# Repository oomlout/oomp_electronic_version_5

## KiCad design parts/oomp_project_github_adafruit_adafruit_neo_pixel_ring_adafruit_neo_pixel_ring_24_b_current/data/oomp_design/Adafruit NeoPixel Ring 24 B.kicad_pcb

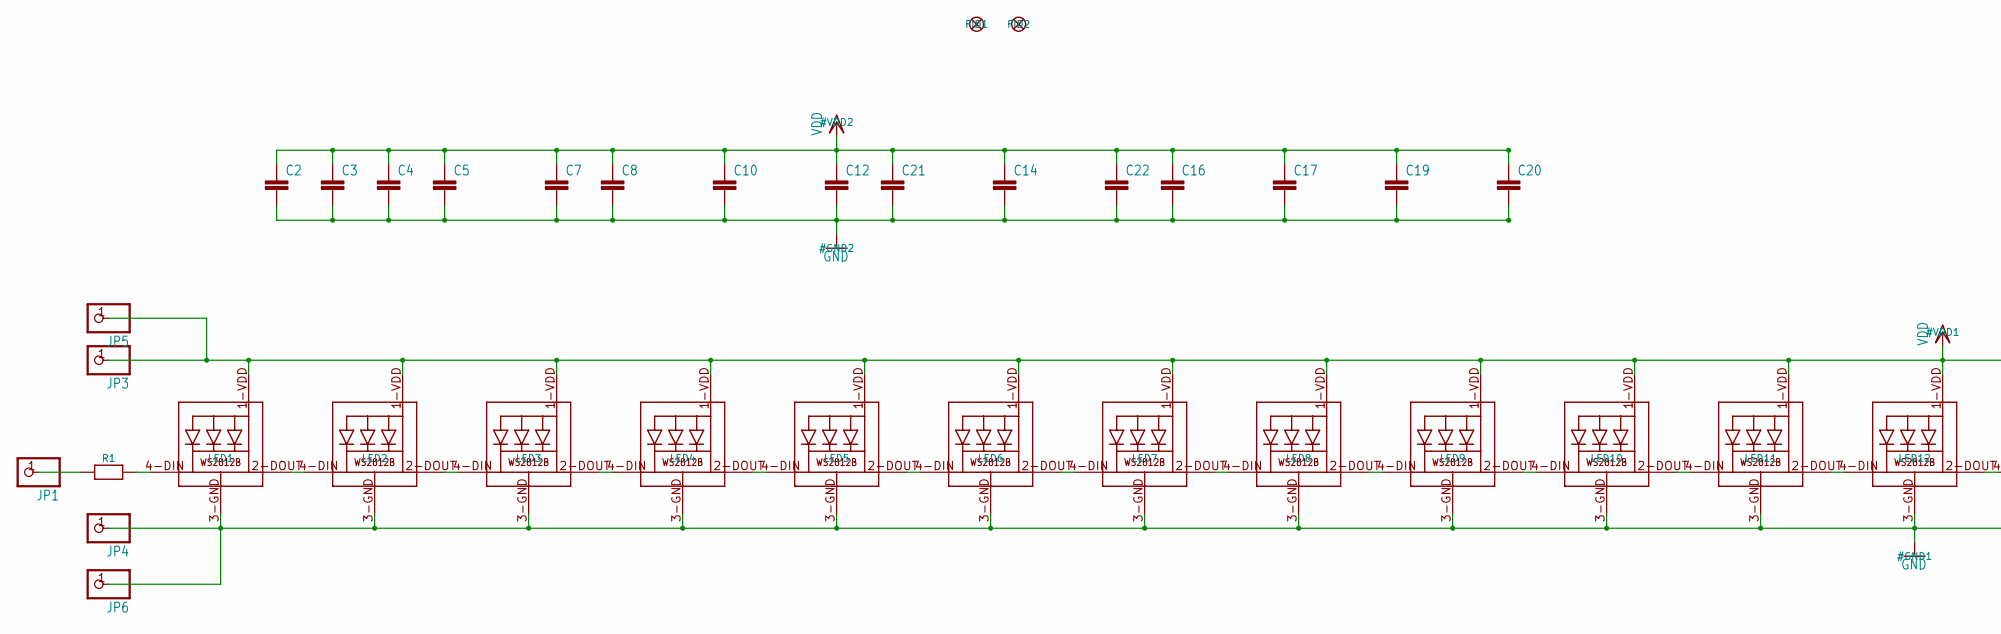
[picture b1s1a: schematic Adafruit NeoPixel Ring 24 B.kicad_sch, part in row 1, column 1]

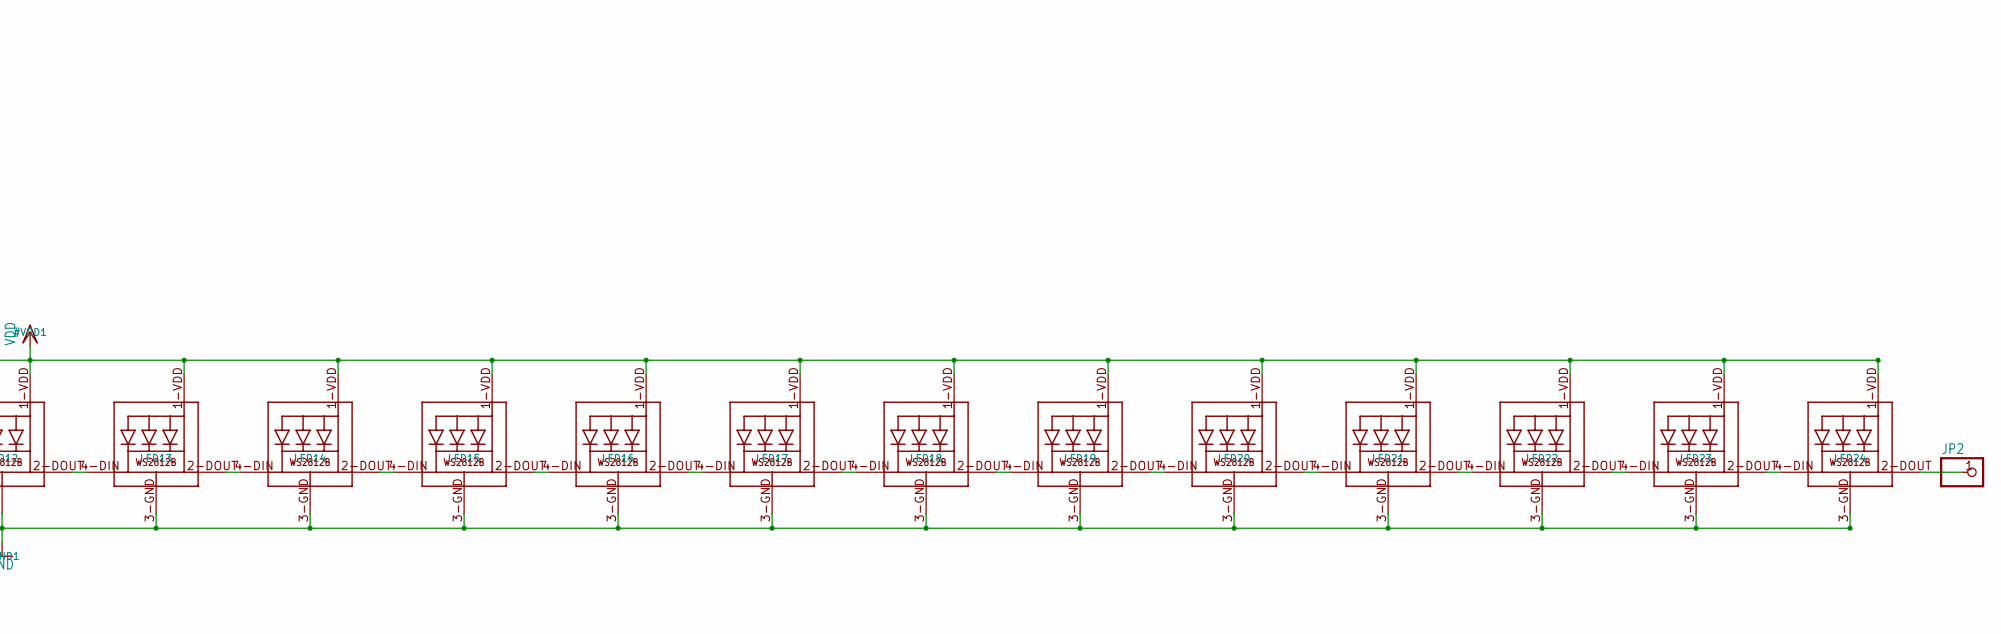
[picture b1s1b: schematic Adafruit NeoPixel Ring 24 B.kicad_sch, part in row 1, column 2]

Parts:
C2, C3, C4, C5, C7, C8, C10, C12, C14, C16, C17, C19, C20, C21, C22: C-EUC0603; C0603
FID1, FID2: FIDUCIAL""; FIDUCIAL_1MM
JP1, JP2, JP3, JP4, JP5, JP6: PINHD-1X1CB; 1X01-CLEANBIG
LED1, LED2, LED3, LED4, LED5, LED6, LED7, LED8, LED9, LED10, LED11, LED12, LED13, LED14, LED15, LED16, LED17, LED18, LED19, LED20, LED21, LED22, LED23, LED24: WS2812B5050; WS2812B
R1: RESISTOR_0603_NOOUT; 0603-NO

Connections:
GND: C2.2, C3.2, C4.2, C5.2, C7.2, C8.2, C10.2, C12.2, C14.2, C16.2, C17.2, C19.2, C20.2, C21.2, C22.2, JP4.1, JP6.1, LED1.3-GND (GND), LED2.3-GND (GND), LED3.3-GND (GND), LED4.3-GND (GND), LED5.3-GND (GND), LED6.3-GND (GND), LED7.3-GND (GND), LED8.3-GND (GND), LED9.3-GND (GND), LED10.3-GND (GND), LED11.3-GND (GND), LED12.3-GND (GND), LED13.3-GND (GND), LED14.3-GND (GND), LED15.3-GND (GND), LED16.3-GND (GND), LED17.3-GND (GND), LED18.3-GND (GND), LED19.3-GND (GND), LED20.3-GND (GND), LED21.3-GND (GND), LED22.3-GND (GND), LED23.3-GND (GND), LED24.3-GND (GND)
unnamed: LED1.2-DOUT (DO), LED2.4-DIN (DI)
unnamed: LED2.2-DOUT (DO), LED3.4-DIN (DI)
unnamed: LED3.2-DOUT (DO), LED4.4-DIN (DI)
unnamed: LED4.2-DOUT (DO), LED5.4-DIN (DI)
unnamed: LED5.2-DOUT (DO), LED6.4-DIN (DI)
unnamed: LED6.2-DOUT (DO), LED7.4-DIN (DI)
unnamed: LED7.2-DOUT (DO), LED8.4-DIN (DI)
unnamed: LED8.2-DOUT (DO), LED9.4-DIN (DI)
unnamed: LED9.2-DOUT (DO), LED10.4-DIN (DI)
unnamed: LED10.2-DOUT (DO), LED11.4-DIN (DI)
unnamed: LED11.2-DOUT (DO), LED12.4-DIN (DI)
unnamed: LED12.2-DOUT (DO), LED13.4-DIN (DI)
unnamed: LED13.2-DOUT (DO), LED14.4-DIN (DI)
unnamed: LED14.2-DOUT (DO), LED15.4-DIN (DI)
unnamed: LED15.2-DOUT (DO), LED16.4-DIN (DI)
unnamed: LED16.2-DOUT (DO), LED17.4-DIN (DI)
unnamed: LED17.2-DOUT (DO), LED18.4-DIN (DI)
unnamed: LED18.2-DOUT (DO), LED19.4-DIN (DI)
unnamed: LED19.2-DOUT (DO), LED20.4-DIN (DI)
unnamed: LED20.2-DOUT (DO), LED21.4-DIN (DI)
unnamed: LED21.2-DOUT (DO), LED22.4-DIN (DI)
unnamed: LED22.2-DOUT (DO), LED23.4-DIN (DI)
unnamed: LED23.2-DOUT (DO), LED24.4-DIN (DI)
unnamed: JP2.1, LED24.2-DOUT (DO)
unnamed: LED1.4-DIN (DI), R1.2
unnamed: JP1.1, R1.1
VDD: C2.1, C3.1, C4.1, C5.1, C7.1, C8.1, C10.1, C12.1, C14.1, C16.1, C17.1, C19.1, C20.1, C21.1, C22.1, JP3.1, JP5.1, LED1.1-VDD (VDD), LED2.1-VDD (VDD), LED3.1-VDD (VDD), LED4.1-VDD (VDD), LED5.1-VDD (VDD), LED6.1-VDD (VDD), LED7.1-VDD (VDD), LED8.1-VDD (VDD), LED9.1-VDD (VDD), LED10.1-VDD (VDD), LED11.1-VDD (VDD), LED12.1-VDD (VDD), LED13.1-VDD (VDD), LED14.1-VDD (VDD), LED15.1-VDD (VDD), LED16.1-VDD (VDD), LED17.1-VDD (VDD), LED18.1-VDD (VDD), LED19.1-VDD (VDD), LED20.1-VDD (VDD), LED21.1-VDD (VDD), LED22.1-VDD (VDD), LED23.1-VDD (VDD), LED24.1-VDD (VDD)

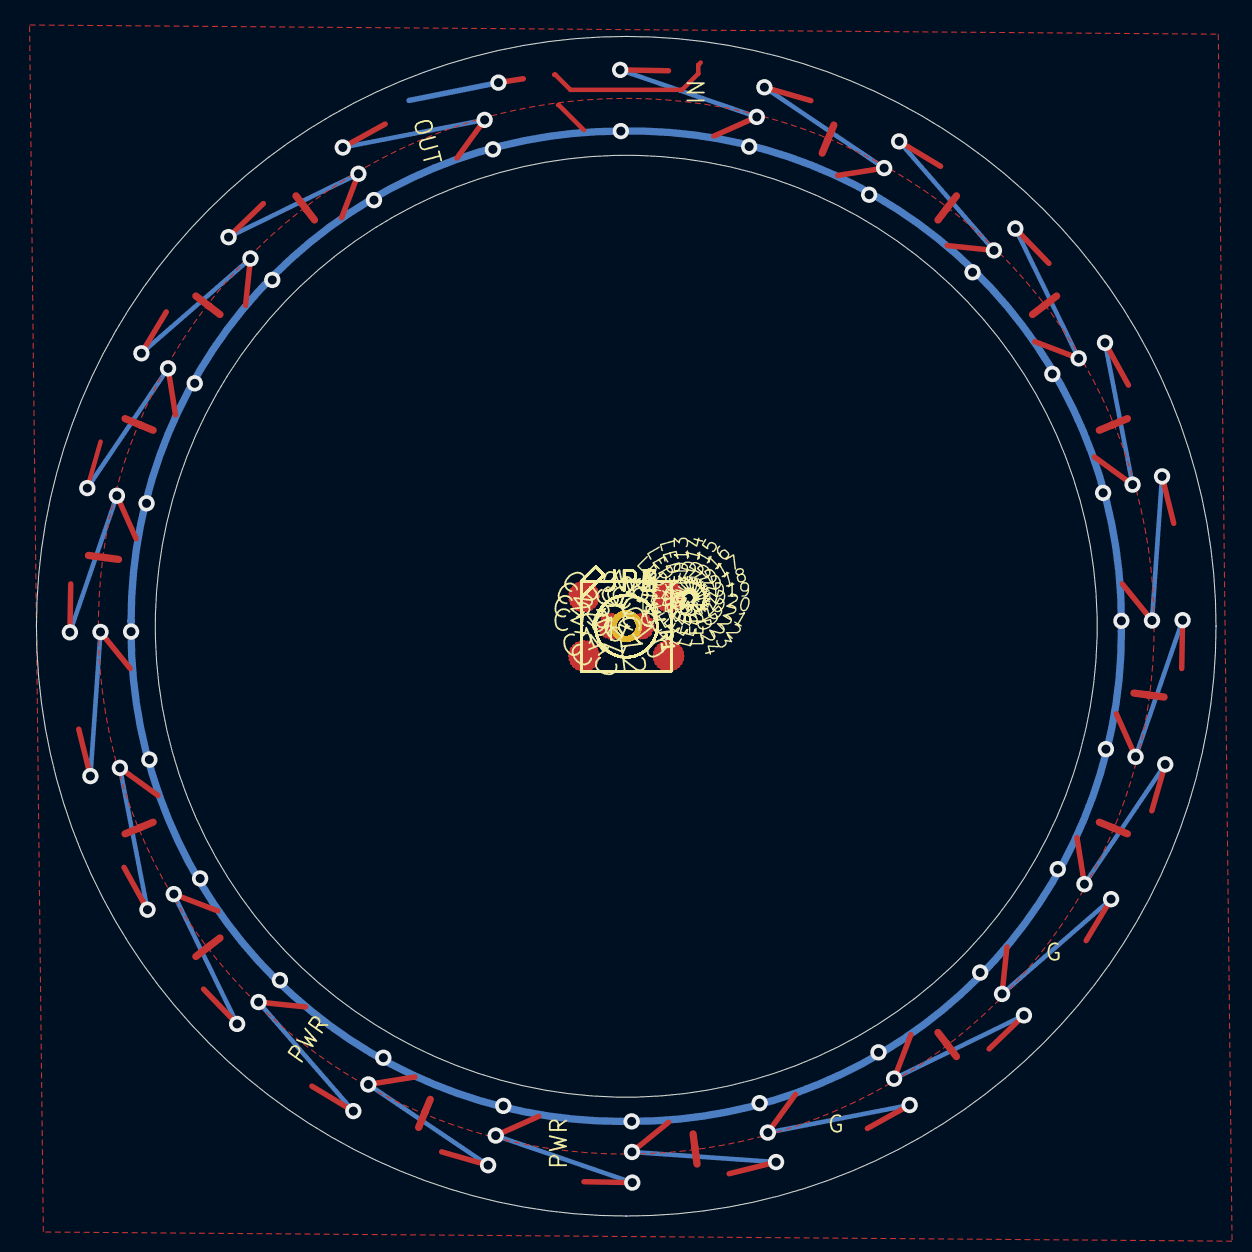
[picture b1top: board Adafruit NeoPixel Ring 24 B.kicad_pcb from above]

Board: 2 copper layers, 65.5 x 65.5 mm, 49 parts (1 on the bottom side), 28 nets.

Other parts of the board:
U$1: ADAFRUIT_5MM

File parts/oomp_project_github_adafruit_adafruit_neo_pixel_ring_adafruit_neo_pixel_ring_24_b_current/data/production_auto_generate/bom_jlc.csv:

Comment,Designator,Footprint,LCSC Part #
,R1,Adafruit NeoPixel Ring 24 B-import-fps:0603-NO,
,"JP1,JP2,JP3,JP4,JP5,JP6",Adafruit NeoPixel Ring 24 B-import-fps:1X01-CLEANBIG,C7501259
,U$1,Adafruit NeoPixel Ring 24 B-import-fps:ADAFRUIT_5MM,
,"C2,C3,C4,C5,C7,C8,C10,C12,C14,C16,C17,C19,C20,C21,C22",Adafruit NeoPixel Ring 24 B-import-fps:C0603,
WS2812B5050,"LED1,LED2,LED3,LED4,LED5,LED6,LED7,LED8,LED9,LED10,LED11,LED12,LED13,LED14,LED15,LED16,LED17,LED18,LED19,LED20,LED21,LED22,LED23,LED24",Adafruit NeoPixel Ring 24 B-import-fps:WS2812B-NARROW,

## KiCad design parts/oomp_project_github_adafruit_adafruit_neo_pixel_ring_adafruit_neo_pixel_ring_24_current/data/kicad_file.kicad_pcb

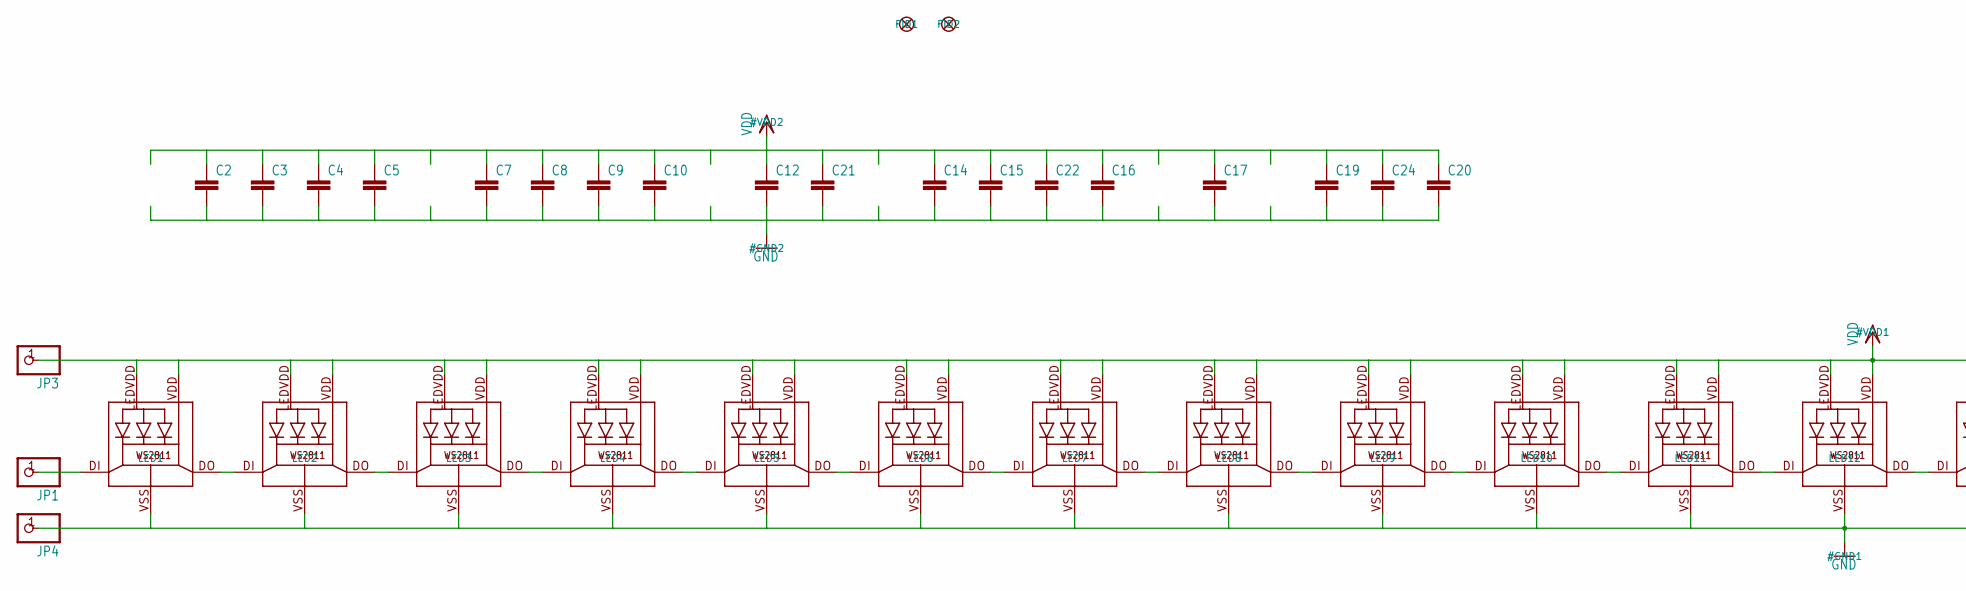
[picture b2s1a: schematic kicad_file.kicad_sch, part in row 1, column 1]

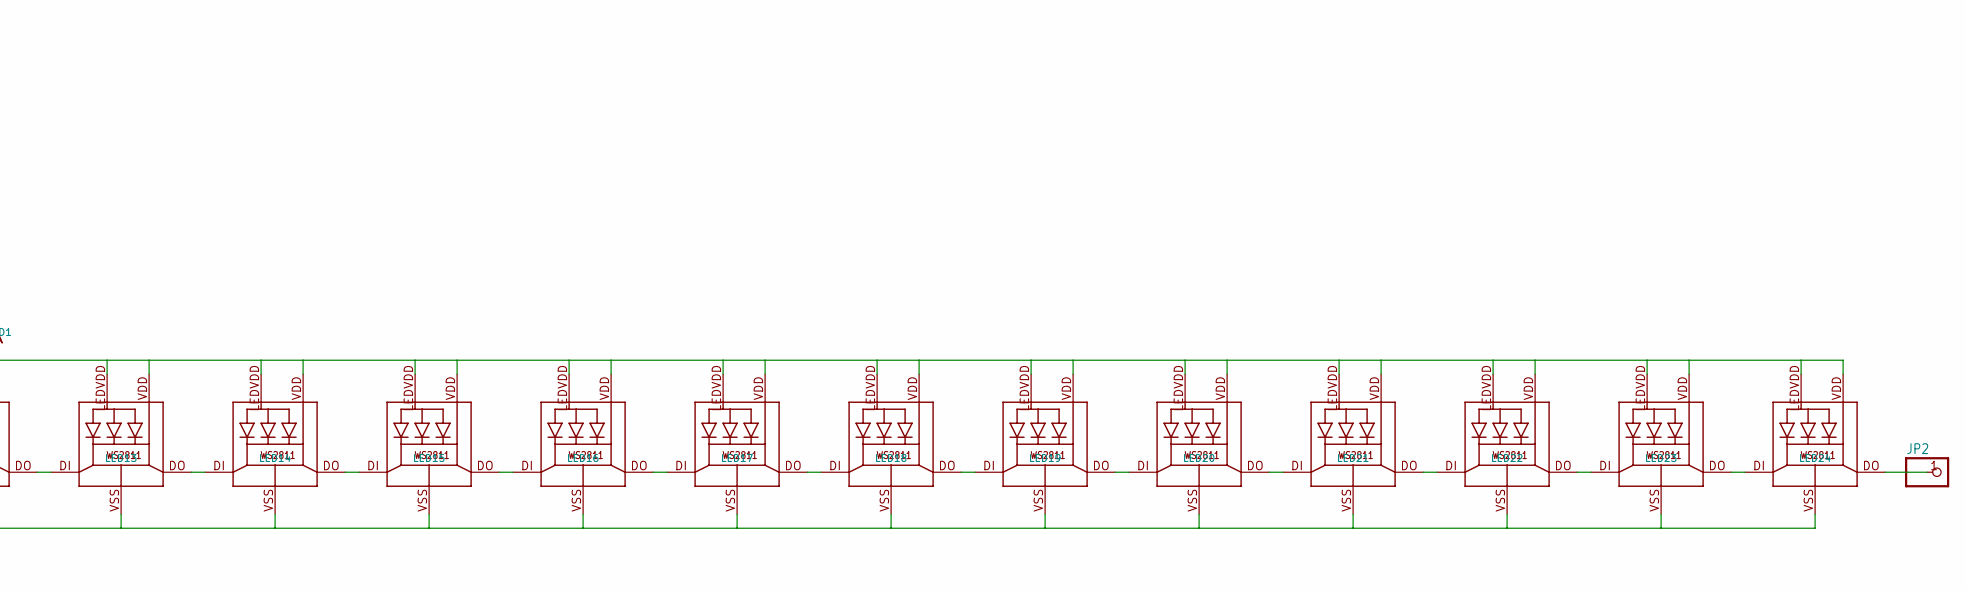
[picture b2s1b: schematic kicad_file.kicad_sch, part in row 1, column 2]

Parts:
C2, C3, C4, C5, C7, C8, C9, C10, C12, C14, C15, C16, C17, C19, C20, C21, C22, C24: C-EUC0603; C0603
FID1, FID2: FIDUCIAL""; FIDUCIAL_1MM
JP1, JP2, JP3, JP4: PINHD-1X1CB; 1X01-CLEANBIG
LED1, LED2, LED3, LED4, LED5, LED6, LED7, LED8, LED9, LED10, LED11, LED12, LED13, LED14, LED15, LED16, LED17, LED18, LED19, LED20, LED21, LED22, LED23, LED24: WS28115050

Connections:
GND: C2.2, C3.2, C4.2, C5.2, C7.2, C8.2, C9.2, C10.2, C12.2, C14.2, C15.2, C16.2, C17.2, C19.2, C20.2, C21.2, C22.2, C24.2, JP4.1, LED1.VSS (GND), LED2.VSS (GND), LED3.VSS (GND), LED4.VSS (GND), LED5.VSS (GND), LED6.VSS (GND), LED7.VSS (GND), LED8.VSS (GND), LED9.VSS (GND), LED10.VSS (GND), LED11.VSS (GND), LED12.VSS (GND), LED13.VSS (GND), LED14.VSS (GND), LED15.VSS (GND), LED16.VSS (GND), LED17.VSS (GND), LED18.VSS (GND), LED19.VSS (GND), LED20.VSS (GND), LED21.VSS (GND), LED22.VSS (GND), LED23.VSS (GND), LED24.VSS (GND)
unnamed: LED1.DO, LED2.DI
unnamed: LED2.DO, LED3.DI
unnamed: LED3.DO, LED4.DI
unnamed: LED4.DO, LED5.DI
unnamed: LED5.DO, LED6.DI
unnamed: LED6.DO, LED7.DI
unnamed: LED7.DO, LED8.DI
unnamed: LED8.DO, LED9.DI
unnamed: LED9.DO, LED10.DI
unnamed: LED10.DO, LED11.DI
unnamed: LED11.DO, LED12.DI
unnamed: LED12.DO, LED13.DI
unnamed: LED13.DO, LED14.DI
unnamed: LED14.DO, LED15.DI
unnamed: LED15.DO, LED16.DI
unnamed: LED16.DO, LED17.DI
unnamed: LED17.DO, LED18.DI
unnamed: LED18.DO, LED19.DI
unnamed: LED19.DO, LED20.DI
unnamed: LED20.DO, LED21.DI
unnamed: LED21.DO, LED22.DI
unnamed: LED22.DO, LED23.DI
unnamed: LED23.DO, LED24.DI
unnamed: JP2.1, LED24.DO
unnamed: JP1.1, LED1.DI
VDD: C2.1, C3.1, C4.1, C5.1, C7.1, C8.1, C9.1, C10.1, C12.1, C14.1, C15.1, C16.1, C17.1, C19.1, C20.1, C21.1, C22.1, C24.1, JP3.1, LED1.LEDVDD, LED1.VDD, LED2.LEDVDD, LED2.VDD, LED3.LEDVDD, LED3.VDD, LED4.LEDVDD, LED4.VDD, LED5.LEDVDD, LED5.VDD, LED6.LEDVDD, LED6.VDD, LED7.LEDVDD, LED7.VDD, LED8.LEDVDD, LED8.VDD, LED9.LEDVDD, LED9.VDD, LED10.LEDVDD, LED10.VDD, LED11.LEDVDD, LED11.VDD, LED12.LEDVDD, LED12.VDD, LED13.LEDVDD, LED13.VDD, LED14.LEDVDD, LED14.VDD, LED15.LEDVDD, LED15.VDD, LED16.LEDVDD, LED16.VDD, LED17.LEDVDD, LED17.VDD, LED18.LEDVDD, LED18.VDD, LED19.LEDVDD, LED19.VDD, LED20.LEDVDD, LED20.VDD, LED21.LEDVDD, LED21.VDD, LED22.LEDVDD, LED22.VDD, LED23.LEDVDD, LED23.VDD, LED24.LEDVDD, LED24.VDD

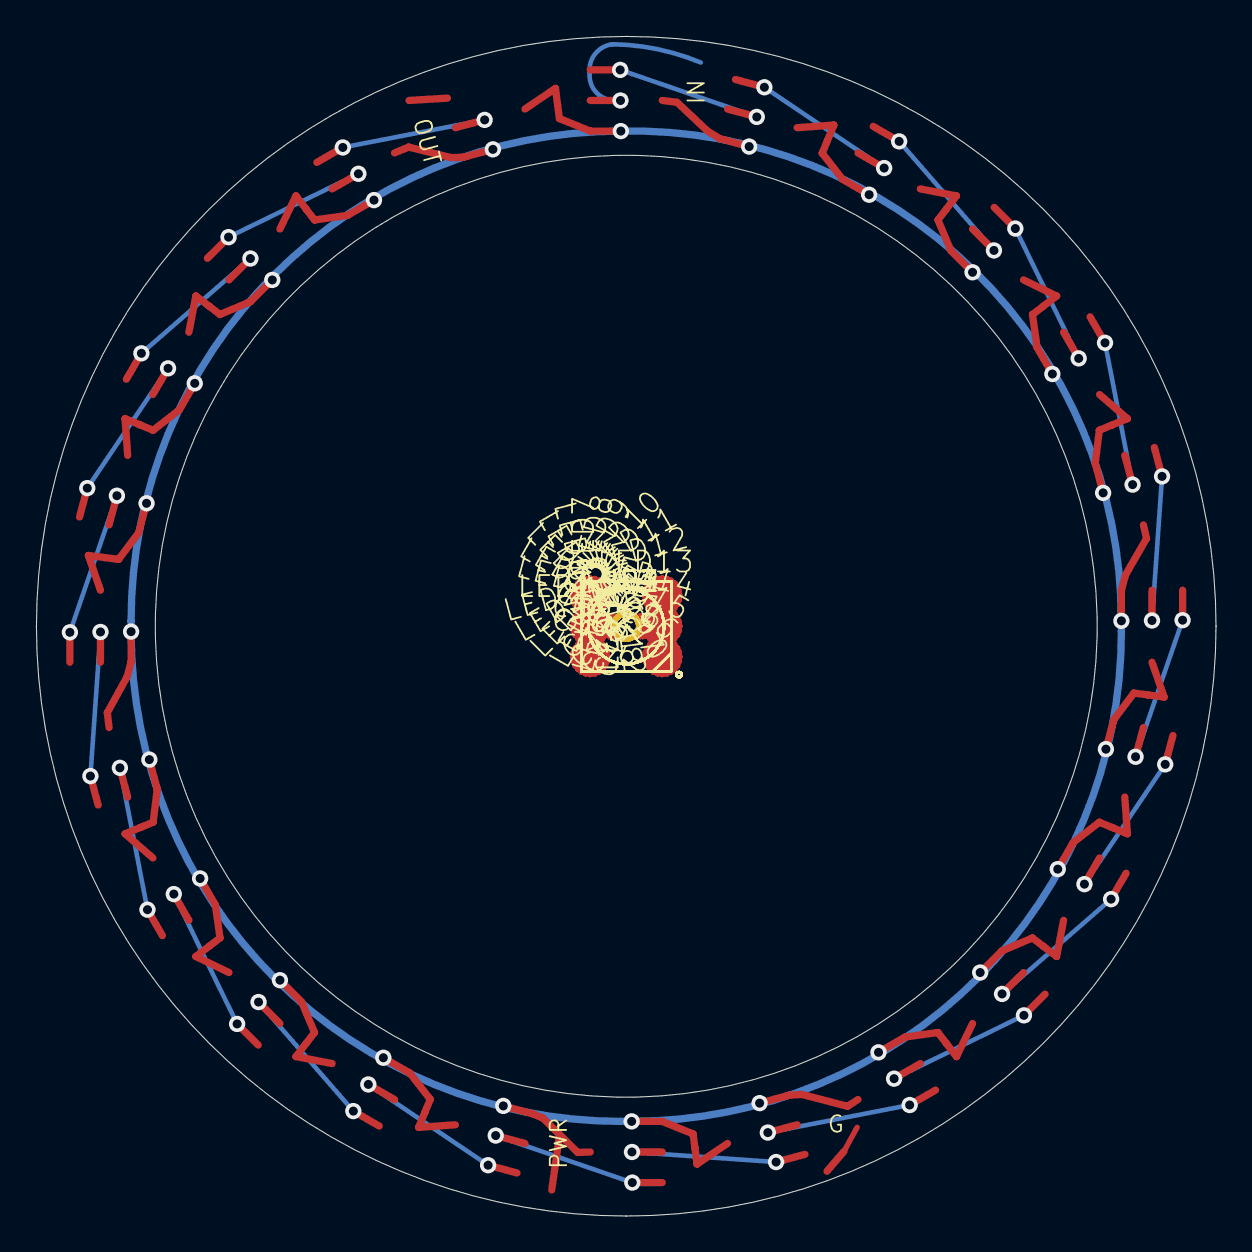
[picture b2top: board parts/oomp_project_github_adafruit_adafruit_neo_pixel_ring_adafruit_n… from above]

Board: 2 copper layers, 65.5 x 65.5 mm, 49 parts (1 on the bottom side), 27 nets.

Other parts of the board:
U$1: ADAFRUIT_5MM

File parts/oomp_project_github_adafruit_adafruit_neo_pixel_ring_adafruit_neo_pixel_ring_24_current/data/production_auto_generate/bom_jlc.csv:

Comment,Designator,Footprint,LCSC Part #
,"JP1,JP2,JP3,JP4",Adafruit NeoPixel Ring 24-import-fps:1X01-CLEANBIG,C7501259
,U$1,Adafruit NeoPixel Ring 24-import-fps:ADAFRUIT_5MM,
,"C2,C3,C4,C5,C7,C8,C9,C10,C12,C14,C15,C16,C17,C19,C20,C21,C22,C24",Adafruit NeoPixel Ring 24-import-fps:C0603,
WS28115050,"LED1,LED2,LED3,LED4,LED5,LED6,LED7,LED8,LED9,LED10,LED11,LED12,LED13,LED14,LED15,LED16,LED17,LED18,LED19,LED20,LED21,LED22,LED23,LED24",Adafruit NeoPixel Ring 24-import-fps:WS28115050,

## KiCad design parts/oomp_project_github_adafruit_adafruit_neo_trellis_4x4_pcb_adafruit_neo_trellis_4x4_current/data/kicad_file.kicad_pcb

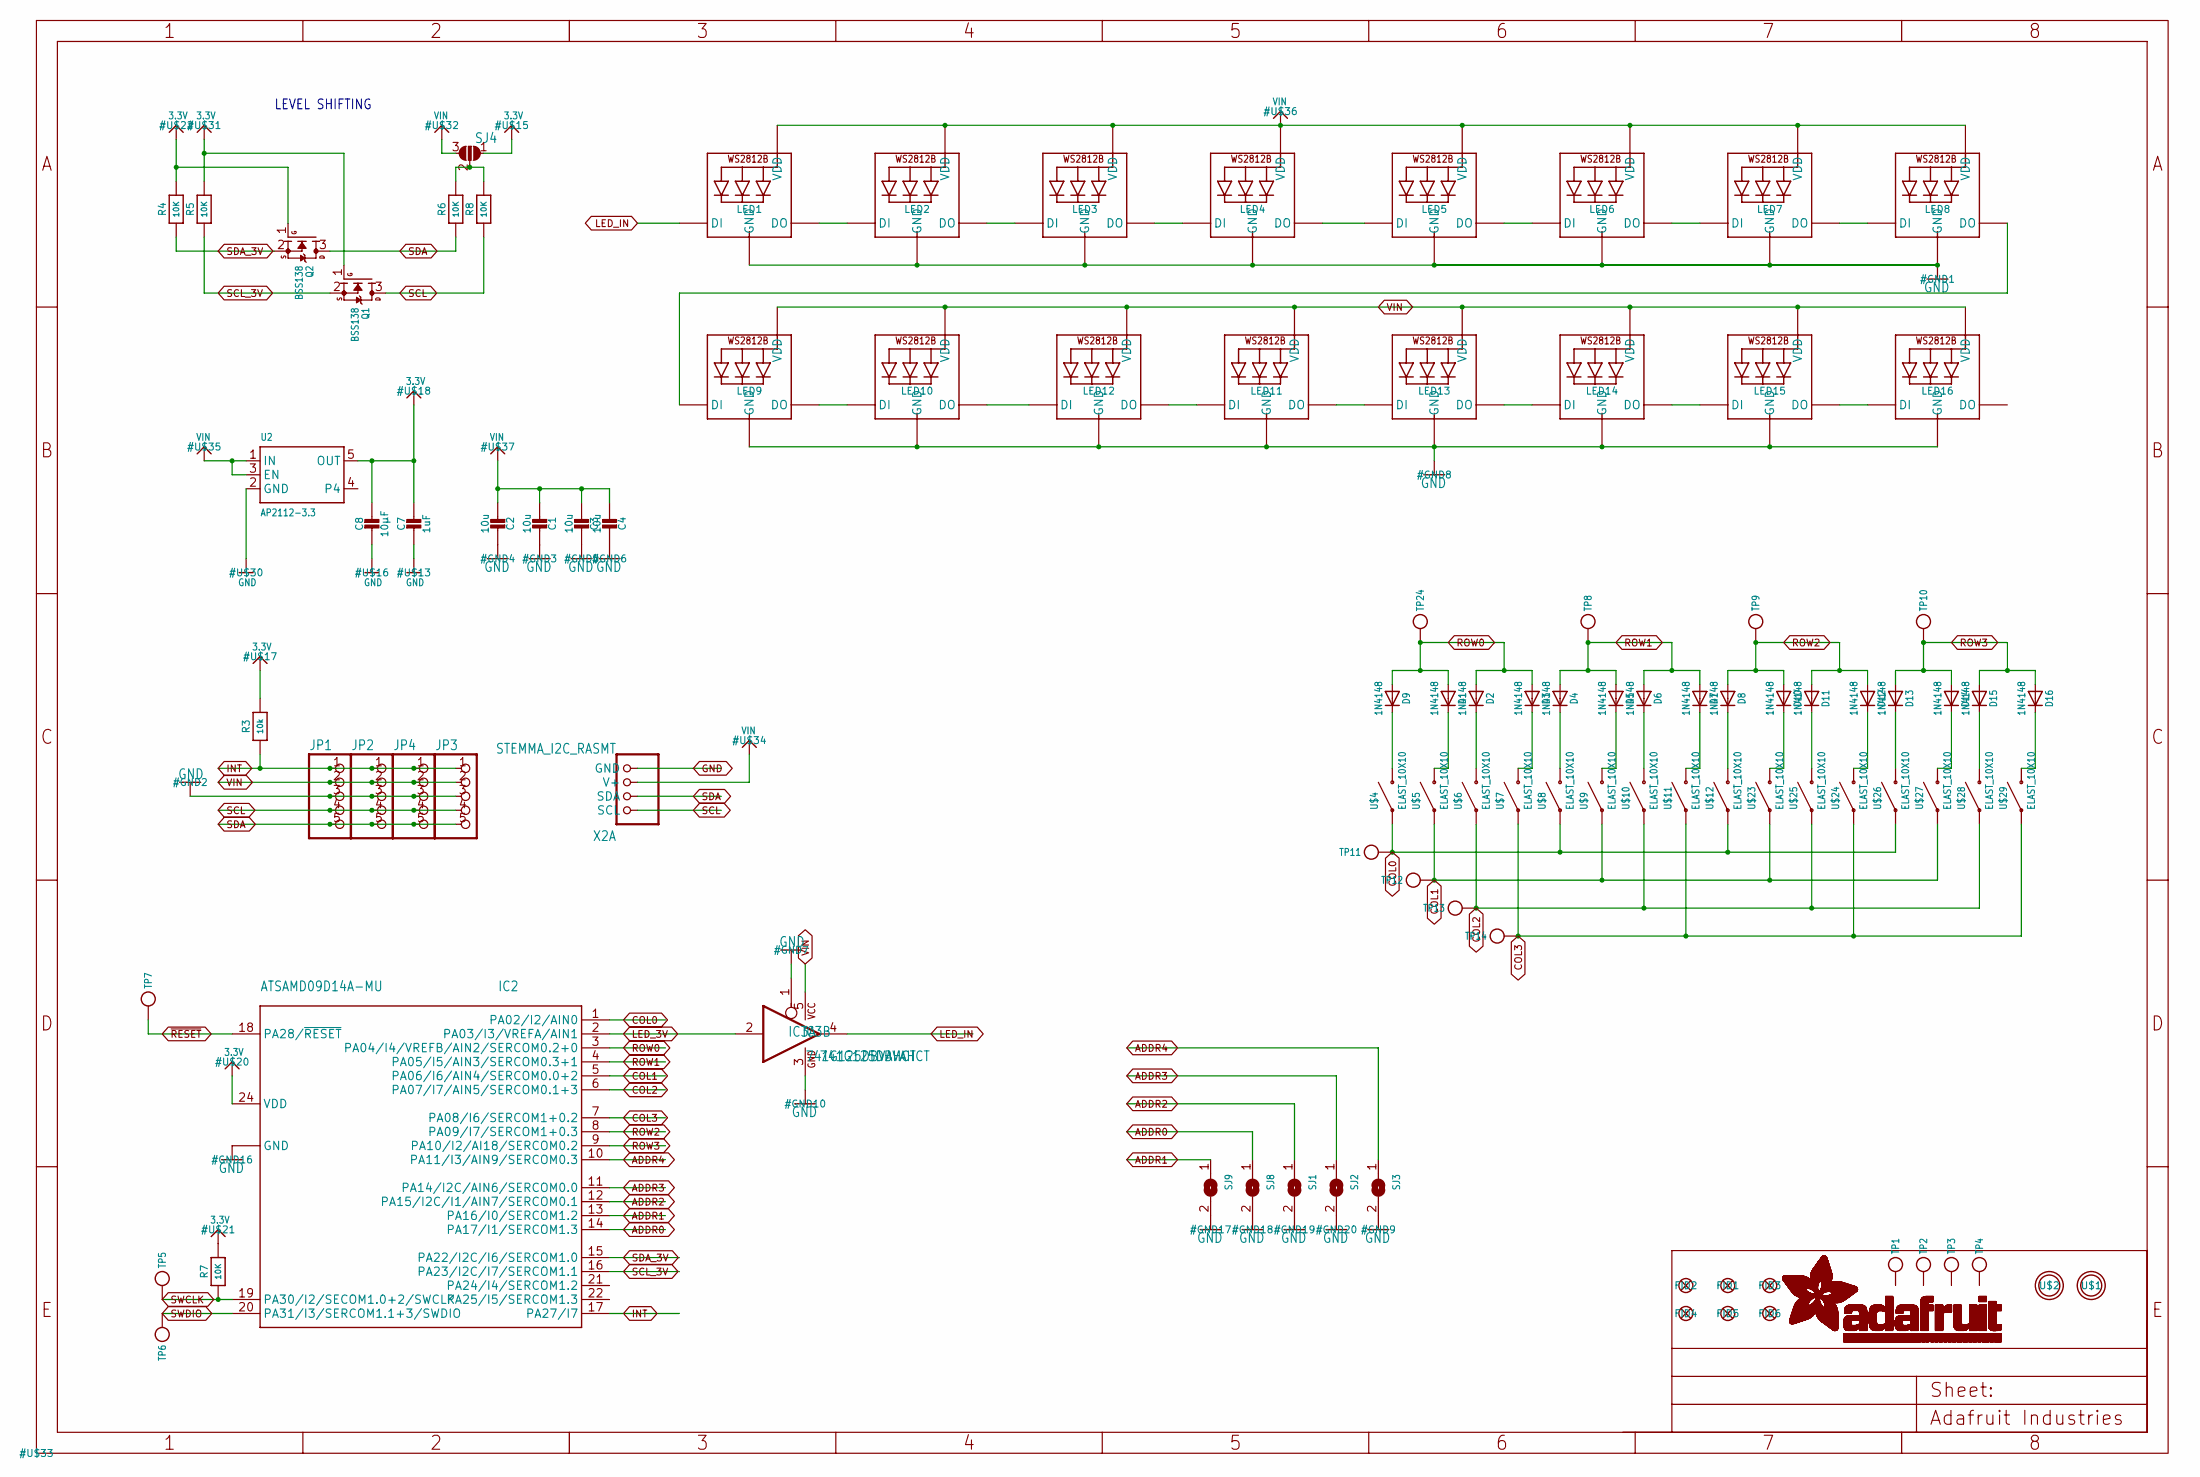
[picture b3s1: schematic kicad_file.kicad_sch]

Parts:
C1, C2, C3, C4: 10u; 0805-NO
C7: 1uF; 0603-NO
C8: 10µF; 0805-NO
D1, D2, D3, D4, D5, D6, D7, D8, D9, D10, D11, D12, D13, D14, D15, D16: 1N4148; SOD-323
FID1, FID2, FID3, FID4, FID5, FID6: FIDUCIAL_1MM
IC2: ATSAMD09D14A-MU; QFN24_4MM
IC3: 741G125DBVAHCT; SOT23-5
JP1, JP2, JP3, JP4: HEADER-1X5EDGESMT; 5P_EDGECONNECT
LED1, LED2, LED3, LED4, LED5, LED6, LED7, LED8, LED9, LED10, LED11, LED12, LED13, LED14, LED15, LED16: WS2812B3535; LED3535
Q1, Q2: BSS138; SOT23-WIDE
R3: 10k; 0603-NO
R4, R5, R6, R7, R8: 10K; 0603-NO
SJ1, SJ2, SJ3, SJ8, SJ9: SOLDERJUMPER; SOLDERJUMPER_ARROW_NOPASTE
SJ4: SOLDERJUMPER_2WAY; SOLDERJUMPER_2WAY_OPEN_NOPASTE
TP1, TP2, TP3, TP4: TESTPOINT; TESTPOINT_SMT
TP5, TP6: TESTPOINTROUND2MM; TESTPOINT_ROUND_2MM
TP7, TP8, TP9, TP10, TP11, TP12, TP13, TP14, TP24: TESTPOINTROUND1.5MM; TESTPOINT_ROUND_1.5MM
U2: AP2112-3.3; SOT23-5
U$1, U$2: MOUNTINGHOLE2.5; MOUNTINGHOLE_2.5_PLATED
U$4, U$5, U$6, U$7, U$8, U$9, U$10, U$11, U$12, U$23, U$24, U$25, U$26, U$27, U$28, U$29: ELAST_10X10; ELAST_PAD_SQUARE_10MM_4X4WIDE
X2: STEMMA_I2C_RASMT; JSTPH4

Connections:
3.3V: C7.1, C8.1, IC2.24 (VDD), Q1.1 (G), Q2.1 (G), R3.2, R4.2, R5.2, R7.2, SJ4.1, U2.5 (OUT)
ADDR0: IC2.14 (PA17/I1/SERCOM1.3), SJ8.1
ADDR1: IC2.13 (PA16/I0/SERCOM1.2), SJ9.1
ADDR2: IC2.12 (PA15/I2C/I1/AIN7/SERCOM0.1), SJ1.1
ADDR3: IC2.11 (PA14/I2C/AIN6/SERCOM0.0), SJ2.1
ADDR4: IC2.10 (PA11/I3/AIN9/SERCOM0.3), SJ3.1
COL0: IC2.1 (PA02/I2/AIN0), TP11.P$1, U$4.P$1, U$8.P$1, U$12.P$1, U$26.P$1
COL1: IC2.5 (PA06/I6/AIN4/SERCOM0.0+2), TP12.P$1, U$5.P$1, U$9.P$1, U$23.P$1, U$27.P$1
COL2: IC2.6 (PA07/I7/AIN5/SERCOM0.1+3), TP13.P$1, U$6.P$1, U$10.P$1, U$25.P$1, U$28.P$1
COL3: IC2.7 (PA08/I6/SERCOM1+0.2), TP14.P$1, U$7.P$1, U$11.P$1, U$24.P$1, U$29.P$1
GND: C1.1, C2.1, C3.1, C4.1, C7.2, C8.2, IC2.23 (GND), IC2.THERM (GND), IC3.1 (OE), IC3.3 (GND), JP1.3, JP2.3, JP3.3, JP4.3, LED1.4 (GND), LED2.4 (GND), LED3.4 (GND), LED4.4 (GND), LED5.4 (GND), LED6.4 (GND), LED7.4 (GND), LED8.4 (GND), LED9.4 (GND), LED10.4 (GND), LED11.4 (GND), LED12.4 (GND), LED13.4 (GND), LED14.4 (GND), LED15.4 (GND), LED16.4 (GND), SJ1.2, SJ2.2, SJ3.2, SJ8.2, SJ9.2, U2.2 (GND), X2.1 (GND)
INT: IC2.17 (PA27/I7), JP1.1, JP2.1, JP3.1, JP4.1, R3.1
LED_3V: IC2.2 (PA03/I3/VREFA/AIN1), IC3.2 (I)
LED_IN: IC3.4 (O), LED1.1 (DI)
unnamed: R6.2, R8.2, SJ4.2
unnamed: D9.C, U$4.P$2
unnamed: D1.C, U$5.P$2
unnamed: D2.C, U$6.P$2
unnamed: D3.C, U$7.P$2
unnamed: D4.C, U$8.P$2
unnamed: D5.C, U$9.P$2
unnamed: LED1.3 (DO), LED2.1 (DI)
unnamed: LED2.3 (DO), LED3.1 (DI)
unnamed: LED3.3 (DO), LED4.1 (DI)
unnamed: LED4.3 (DO), LED5.1 (DI)
unnamed: D6.C, U$10.P$2
unnamed: LED5.3 (DO), LED6.1 (DI)
unnamed: LED6.3 (DO), LED7.1 (DI)
unnamed: D7.C, U$11.P$2
unnamed: LED7.3 (DO), LED8.1 (DI)
unnamed: D8.C, U$12.P$2
unnamed: LED8.3 (DO), LED9.1 (DI)
unnamed: D10.C, U$23.P$2
unnamed: D11.C, U$25.P$2
unnamed: D12.C, U$24.P$2
unnamed: D13.C, U$26.P$2
unnamed: D14.C, U$27.P$2
unnamed: D15.C, U$28.P$2
unnamed: D16.C, U$29.P$2
unnamed: LED9.3 (DO), LED10.1 (DI)
unnamed: LED10.3 (DO), LED12.1 (DI)
unnamed: LED11.1 (DI), LED12.3 (DO)
unnamed: LED11.3 (DO), LED13.1 (DI)
unnamed: LED13.3 (DO), LED14.1 (DI)
unnamed: LED14.3 (DO), LED15.1 (DI)
unnamed: LED15.3 (DO), LED16.1 (DI)
ROW0: D1.A, D2.A, D3.A, D9.A, IC2.3 (PA04/I4/VREFB/AIN2/SERCOM0.2+0), TP24.P$1
ROW1: D4.A, D5.A, D6.A, D7.A, IC2.4 (PA05/I5/AIN3/SERCOM0.3+1), TP8.P$1
ROW2: D8.A, D10.A, D11.A, D12.A, IC2.8 (PA09/I7/SERCOM1+0.3), TP9.P$1
ROW3: D13.A, D14.A, D15.A, D16.A, IC2.9 (PA10/I2/AI18/SERCOM0.2), TP10.P$1
SCL: JP1.4, JP2.4, JP3.4, JP4.4, Q1.3 (D), R8.1, X2.4 (SCL)
SCL_3V: IC2.16 (PA23/I2C/I7/SERCOM1.1), Q1.2 (S), R5.1
SDA: JP1.5, JP2.5, JP3.5, JP4.5, Q2.3 (D), R6.1, X2.3 (SDA)
SDA_3V: IC2.15 (PA22/I2C/I6/SERCOM1.0), Q2.2 (S), R4.1
SWCLK: IC2.19 (PA30/I2/SECOM1.0+2/SWCLK), R7.1, TP5.P$1
SWDIO: IC2.20 (PA31/I3/SERCOM1.1+3/SWDIO), TP6.P$1
VIN: C1.2, C2.2, C3.2, C4.2, IC3.5 (VCC), JP1.2, JP2.2, JP3.2, JP4.2, LED1.2 (VDD), LED2.2 (VDD), LED3.2 (VDD), LED4.2 (VDD), LED5.2 (VDD), LED6.2 (VDD), LED7.2 (VDD), LED8.2 (VDD), LED9.2 (VDD), LED10.2 (VDD), LED11.2 (VDD), LED12.2 (VDD), LED13.2 (VDD), LED14.2 (VDD), LED15.2 (VDD), LED16.2 (VDD), SJ4.3, U2.1 (IN), U2.3 (EN), X2.2 (V+)
~RESET: IC2.18 (PA28/~RESET), TP7.P$1

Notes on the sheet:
LEVEL SHIFTING

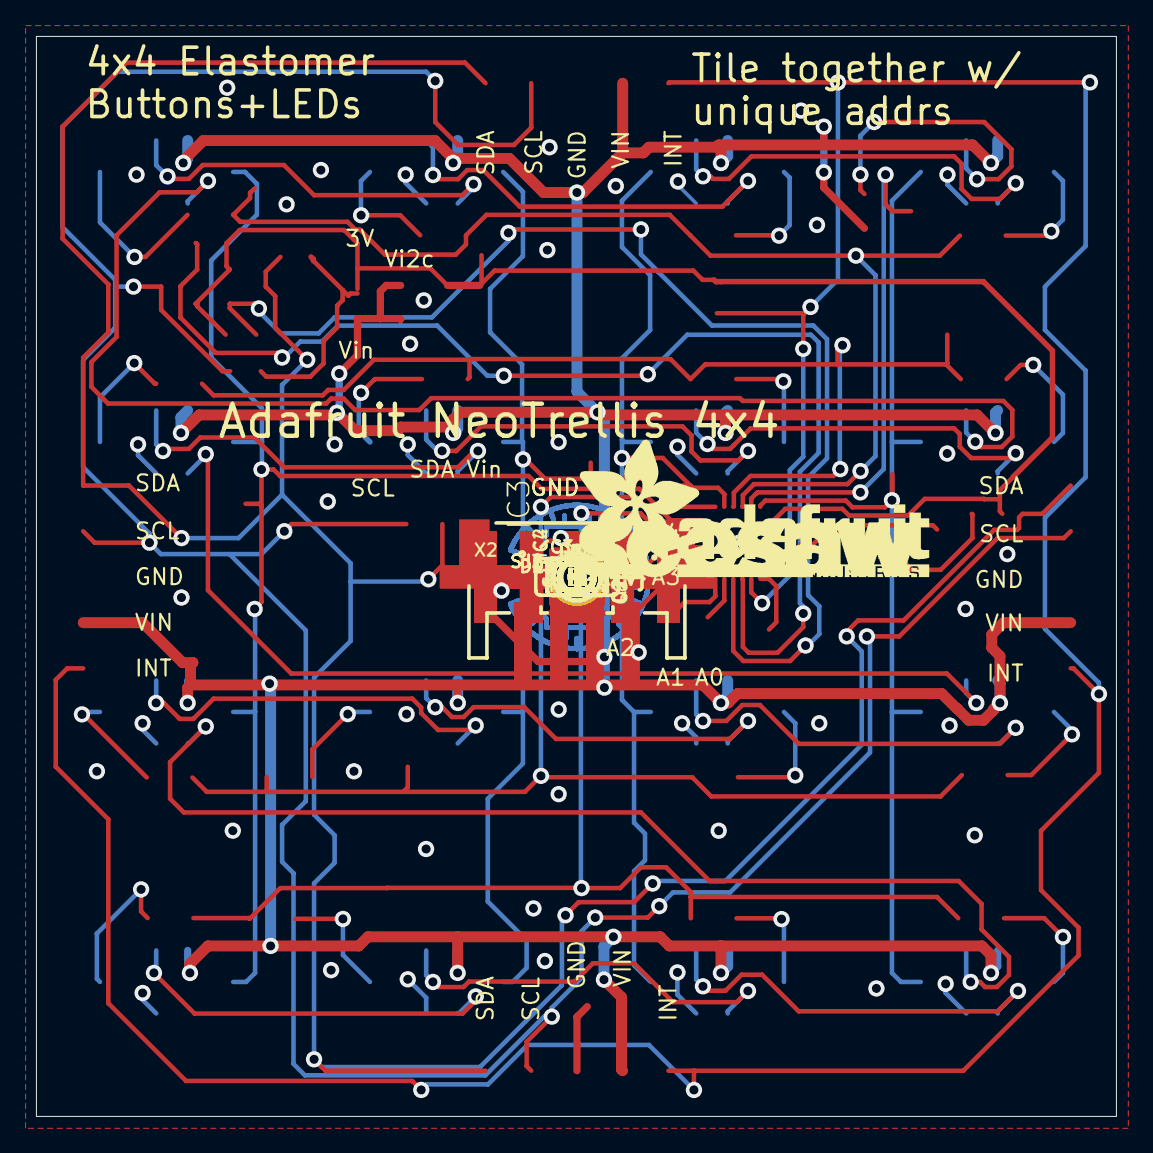
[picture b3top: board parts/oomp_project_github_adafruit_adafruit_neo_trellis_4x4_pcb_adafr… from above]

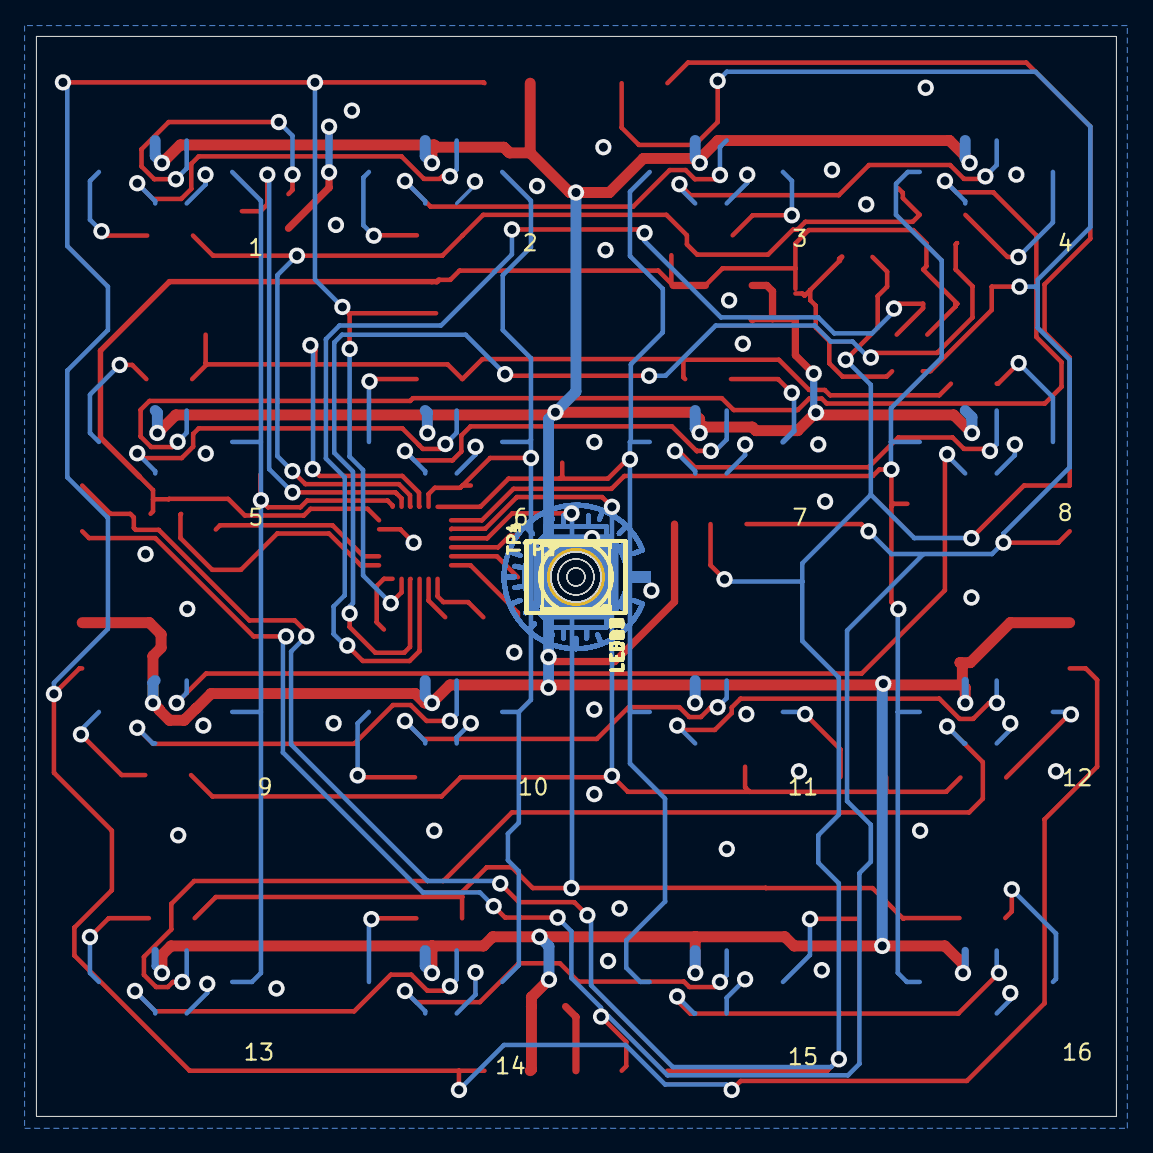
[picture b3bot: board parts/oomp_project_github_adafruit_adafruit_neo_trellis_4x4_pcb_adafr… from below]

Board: 2 copper layers, 60.0 x 60.0 mm, 118 parts (41 on the bottom side), 58 nets.

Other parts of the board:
U$3: ADAFRUIT_TEXT_20MM
U$14: SEESAW_LOGO
U$19: PCBFEAT-REV-040
UNK_HOLE_0: dummyfp0
UNK_HOLE_1: dummyfp1
UNK_HOLE_2: dummyfp2
UNK_HOLE_3: dummyfp3
UNK_HOLE_4: dummyfp4
UNK_HOLE_5: dummyfp5
UNK_HOLE_6: dummyfp6
UNK_HOLE_7: dummyfp7
UNK_HOLE_8: dummyfp8
UNK_HOLE_9: dummyfp9
UNK_HOLE_10: dummyfp10
UNK_HOLE_11: dummyfp11
UNK_HOLE_12: dummyfp12
UNK_HOLE_13: dummyfp13
UNK_HOLE_14: dummyfp14
UNK_HOLE_15: dummyfp15

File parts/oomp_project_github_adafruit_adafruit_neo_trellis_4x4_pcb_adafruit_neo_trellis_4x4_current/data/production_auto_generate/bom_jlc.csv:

Comment,Designator,Footprint,LCSC Part #
,"JP1,JP2,JP3,JP4",Adafruit NeoTrellis 4x4-import-fps:5P_EDGECONNECT,
,U$3,Adafruit NeoTrellis 4x4-import-fps:ADAFRUIT_TEXT_20MM,
,U$19,Adafruit NeoTrellis 4x4-import-fps:PCBFEAT-REV-040,
,U$14,Adafruit NeoTrellis 4x4-import-fps:SEESAW_LOGO,
,"TP7,TP8,TP9,TP10,TP11,TP12,TP13,TP14,TP24",Adafruit NeoTrellis 4x4-import-fps:TESTPOINT_ROUND_1.5MM,
,"TP5,TP6",Adafruit NeoTrellis 4x4-import-fps:TESTPOINT_ROUND_2MM,
,"TP1,TP2,TP3,TP4",Adafruit NeoTrellis 4x4-import-fps:TESTPOINT_SMT,
10k,R3,Adafruit NeoTrellis 4x4-import-fps:0603-NO,C98220
10K,"R4,R5,R6,R7,R8",Adafruit NeoTrellis 4x4-import-fps:0603-NO,C98220
10u,"C1,C2,C3,C4",Adafruit NeoTrellis 4x4-import-fps:0805-NO,
10µF,C8,Adafruit NeoTrellis 4x4-import-fps:0805-NO,
1N4148,"D1,D2,D3,D4,D5,D6,D7,D8,D9,D10,D11,D12,D13,D14,D15,D16",Adafruit NeoTrellis 4x4-import-fps:SOD-323,
1uF,C7,Adafruit NeoTrellis 4x4-import-fps:0603-NO,C5673
74AHCT1G125DBV,IC3,Adafruit NeoTrellis 4x4-import-fps:SOT23-5,
AP2112-3.3,U2,Adafruit NeoTrellis 4x4-import-fps:SOT23-5,
ATSAMD09D14A-MU,IC2,Adafruit NeoTrellis 4x4-import-fps:QFN24_4MM,
BSS138,"Q1,Q2",Adafruit NeoTrellis 4x4-import-fps:SOT23-WIDE,C52895
ELAST_10X10,"U$4,U$5,U$6,U$7,U$8,U$9,U$10,U$11,U$12,U$23,U$24,U$25,U$26,U$27,U$28,U$29",Adafruit NeoTrellis 4x4-import-fps:ELAST_PAD_SQUARE_10MM_4X4WIDE,
STEMMA_I2C_RASMT,X2,Adafruit NeoTrellis 4x4-import-fps:JSTPH4,
WS2812B3535,"LED1,LED2,LED3,LED4,LED5,LED6,LED7,LED8,LED9,LED10,LED11,LED12,LED13,LED14,LED15,LED16",Adafruit NeoTrellis 4x4-import-fps:LED3535,
